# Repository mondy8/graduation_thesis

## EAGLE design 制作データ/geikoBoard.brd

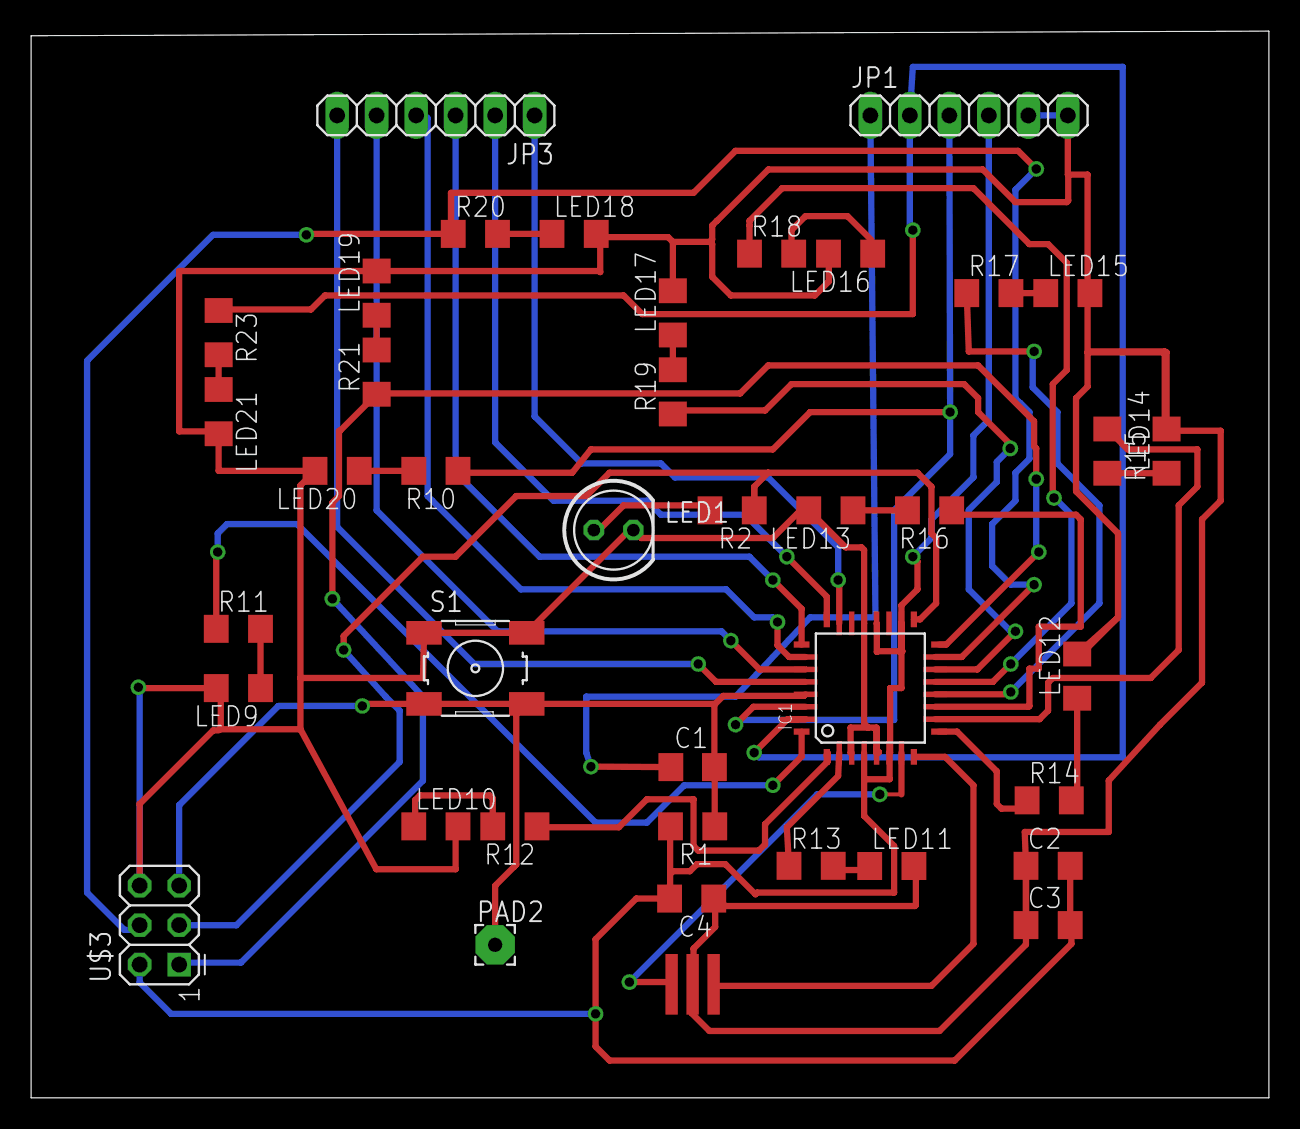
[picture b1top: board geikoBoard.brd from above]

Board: 2 copper layers, 79.6 x 68.6 mm, 40 parts (0 on the bottom side), 40 nets.

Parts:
C1: .1uf; C1206
C2: 1uf; 1206
C3: .1uf; 1206
C4: 10uf; 1206
IC1: ATMEGA48/88/168-AU; TQFP32-08
JP1, JP3: 1X06
LED1: LED5MM
LED9, LED10, LED11, LED12, LED13, LED14, LED15, LED16, LED17, LED18, LED19, LED20, LED21: 1206
PAD2: WIREPAD2,54/0,9; 2,54/0,9
R1: 10k; 1206
R2, R10, R11, R12, R13, R14, R15, R16, R17, R18, R19, R20, R21, R23: 499; 1206
S1: 6MM_SWITCH
U$2: RESONATOREFOB; EFOBM
U$3: AVRISP; 2X03

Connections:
DTR: C1.1, JP1.1
GND: C2.1, C3.1, C4.1, IC1.3, IC1.5, IC1.21, JP1.5, JP1.6, LED1.K, LED9.2, LED10.2, LED11.2, LED12.2, LED13.2, LED14.2, LED15.2, LED16.2, LED17.2, LED18.2, LED19.2, LED20.2, LED21.2, S1.1, S1.2, U$2.2, U$3.6
MISO: IC1.16, R21.1, U$3.1
MOSI: IC1.15, R20.1, U$3.4
unnamed: IC1.8, U$2.1
unnamed: IC1.12, R17.1
unnamed: IC1.23, JP3.1
unnamed: IC1.24, JP3.2
unnamed: IC1.25, JP3.3
unnamed: IC1.26, JP3.4
unnamed: IC1.27, JP3.5
unnamed: IC1.28, JP3.6
unnamed: IC1.7, U$2.3
unnamed: IC1.32, R11.1
unnamed: IC1.1, R12.1
unnamed: IC1.2, R13.1
unnamed: IC1.9, R14.1
unnamed: IC1.10, R15.1
unnamed: IC1.11, R16.1
unnamed: IC1.13, R18.1
unnamed: IC1.14, R19.1
unnamed: LED9.1, R11.2
unnamed: LED10.1, R12.2
unnamed: LED11.1, R13.2
unnamed: LED12.1, R14.2
unnamed: LED1.A, R2.2
unnamed: LED13.1, R16.2
unnamed: LED14.1, R15.2
unnamed: LED15.1, R17.2
unnamed: LED16.1, R18.2
unnamed: LED17.1, R19.2
unnamed: LED18.1, R20.2
unnamed: LED19.1, R21.2
unnamed: LED20.1, R10.2
unnamed: LED21.1, R23.2
RST: C1.2, IC1.29, PAD2.1, R1.1, S1.3, S1.4, U$3.5
RX: IC1.30, JP1.3, R10.1
SCK: IC1.17, R2.1, U$3.3
TX: IC1.31, JP1.2, R23.1
VCC: C2.2, C3.2, C4.2, IC1.4, IC1.6, IC1.18, IC1.20, JP1.4, R1.2, U$3.2

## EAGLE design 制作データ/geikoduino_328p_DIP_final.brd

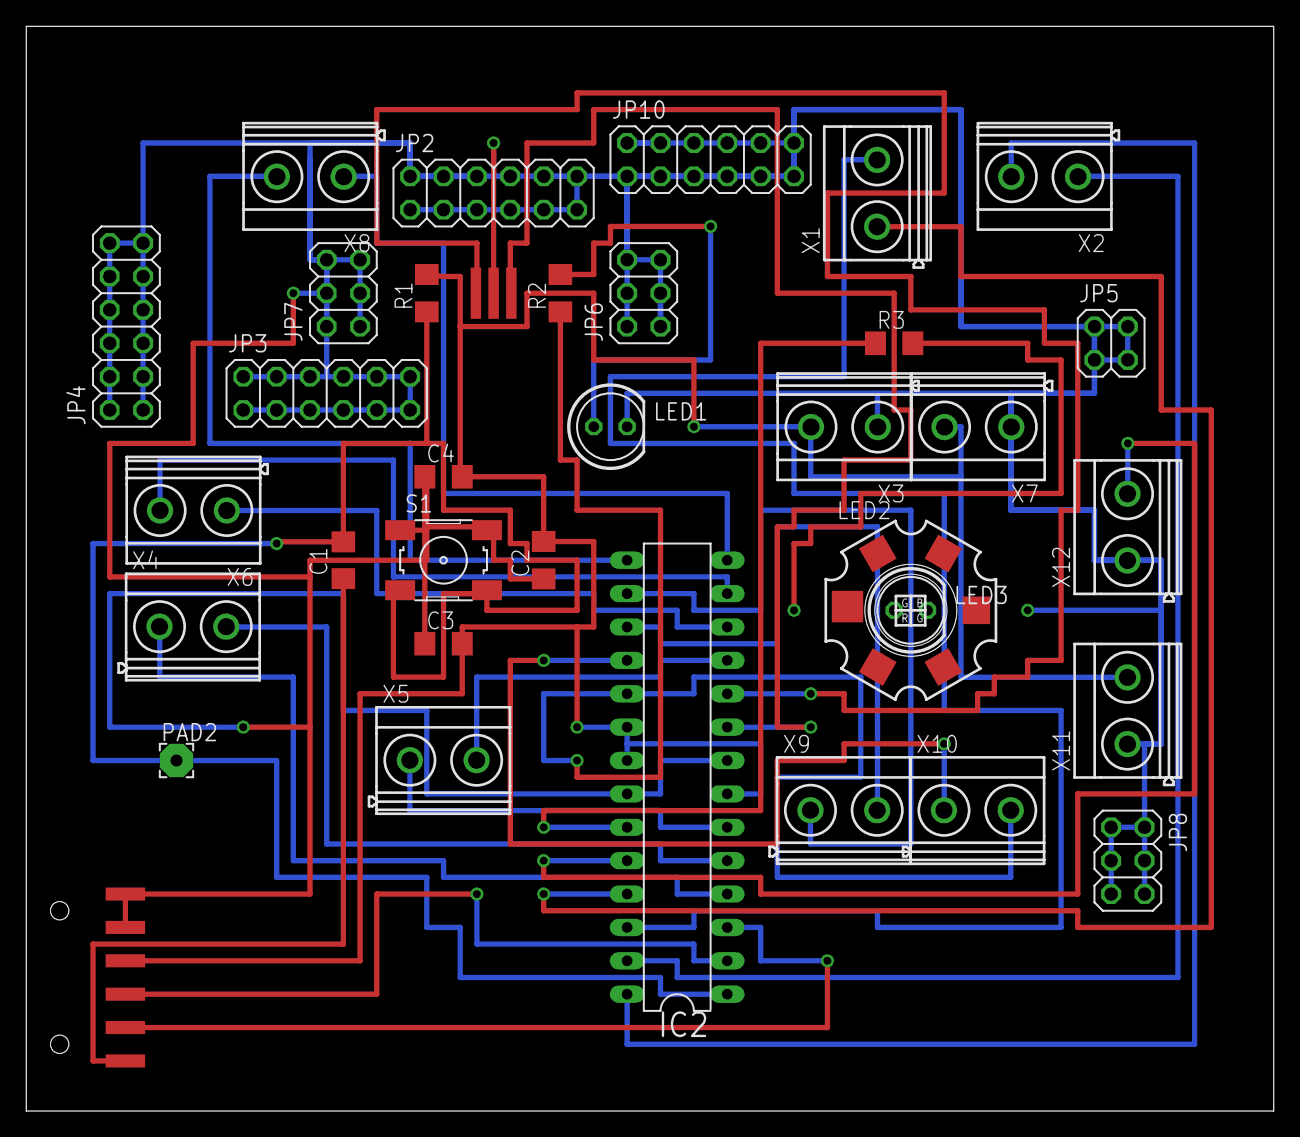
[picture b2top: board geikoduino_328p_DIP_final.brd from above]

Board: 2 copper layers, 94.9 x 82.5 mm, 35 parts (0 on the bottom side), 29 nets.

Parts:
C1: .1uf; C1206
C2: 1uf; 1206
C3: .1uf; 1206
C4: 10uf; 1206
IC2: ATMEGA328-20P; DIL28-3
JP1: 1X06-SMD
JP2, JP3, JP4, JP10: 2X06
JP5: 2X02
JP6, JP7, JP8: 2X03
LED1, LED3: LED5MM
LED2: ACULED-RGB
PAD2: WIREPAD2,54/0,9; 2,54/0,9
R1: 10k; 1206
R2: 499; 1206
R3: 7.14; 1206
S1: 6MM_SWITCH
U$2: RESONATOREFOB; EFOBM
X1, X2, X3, X4, X5, X6, X7, X8, X9, X10, X11, X12: MKDSN1,5/2-5,08

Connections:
DTR: C1.1, JP1.6
GND: C2.1, C3.1, C4.1, IC2.8, IC2.22, JP1.1, JP1.2, JP2.1, JP2.2, JP2.3, JP2.4, JP2.5, JP2.6, JP2.7, JP2.8, JP2.9, JP2.10, JP2.11, JP2.12, JP3.1, JP3.2, JP3.3, JP3.4, JP3.5, JP3.6, JP3.7, JP3.8, JP3.9, JP3.10, JP3.11, JP3.12, JP4.1, JP4.2, JP4.3, JP4.4, JP4.5, JP4.6, JP4.7, JP4.8, JP4.9, JP4.10, JP4.11, JP4.12, JP6.2, JP10.1, JP10.2, JP10.3, JP10.4, JP10.5, JP10.6, JP10.7, JP10.8, JP10.9, JP10.10, JP10.11, JP10.12, LED1.K, LED3.K, S1.1, S1.2, U$2.2, X3.1, X7.1, X11.1, X12.1
MISO: IC2.18, X10.1
MOSI: IC2.17, X9.2
unnamed: IC2.10, U$2.1
unnamed: IC2.14, X8.1
unnamed: IC2.23, R3.1
unnamed: IC2.24, X12.2
unnamed: IC2.25, X1.1
unnamed: IC2.26, X1.2
unnamed: IC2.27, X2.1
unnamed: IC2.28, X2.2
unnamed: IC2.9, U$2.3
unnamed: IC2.4, X4.1
unnamed: IC2.5, X4.2
unnamed: IC2.6, X5.1
unnamed: IC2.11, X5.2
unnamed: IC2.12, X6.1
unnamed: IC2.13, X6.2
unnamed: LED1.A, R2.2
unnamed: IC2.15, X8.2
unnamed: IC2.16, X9.1
unnamed: LED3.A, R3.2
unnamed: JP5.1, JP5.2, JP5.3, JP5.4, JP6.1, JP6.3, JP6.5, JP6.6, JP7.1, JP7.2, JP7.3, JP7.4, JP7.5, JP7.6, JP8.1, JP8.2, JP8.3, JP8.4, JP8.5, JP8.6
RST: C1.2, IC2.1, PAD2.1, R1.1, S1.3, S1.4
RX: IC2.2, JP1.4
SCK: IC2.19, R2.1, X10.2
TX: IC2.3, JP1.5
VCC: C2.2, C3.2, C4.2, IC2.7, IC2.20, IC2.21, JP1.3, R1.2, X3.2, X7.2, X11.2

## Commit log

2016-11-28 実例紹介追加
2016-12-01 背景課題など追加
2016-12-02 背景追加
2016-12-04 背景など追加
2016-12-06 ファイルのワード化 背景追加
2016-12-10 txtデータ削除、材料候補追加、背景を一部構成変更
2016-12-11 目次追加
2016-12-19 基板の歴史追加
2016-12-19 中間発表プレゼン追加
2016-12-28 制作したeagleデータ・画像の追加
2016-12-29 制作過程追加、geikoduino一つ目ミリング終える
2017-01-07 制作過程・基板作成の歴史追加
2017-01-08 １章書き始める
2017-01-09 １章、４章追加
2017-01-09 １章追加・４章を３章に変更
2017-01-10 アンケートを作成・１章と3章を追加
2017-01-15 研究の方向転換・GeikoBoard作成するも挫折
2017-01-17 挫折を乗り越える・概要を追加
2017-01-18 概要追加
2017-01-20 概要提出
2017-01-20 ファイルの整理、本文執筆開始
2017-01-20 本論文の型を作成
2017-01-23 本文執筆
2017-01-24 画像追加
2017-01-24 ユーザー評価を進める
2017-01-25 ユーザー評価更新
2017-01-25 いろいろ画像追加
2017-01-26 考察など追加
2017-01-26 最後らへん追加
2017-01-28 参考文献整理
2017-01-28 図の整理
2017-01-28 ところどころ追加
2017-01-28 第１版完成、か？
2017-01-30 結論の肉付け
2017-01-30 完成！！
2017-02-01 提出完了
2018-12-02 softrobot start
2018-12-17 ファイルの整理・稲研展の準備
2019-01-01 新年一発目 アンケート調査アンド枠組み整理
2019-01-02 シリコン生成方法記入
2019-01-06 3章 heart of mollusca 制作方法について詳細追加
2019-01-06 ４章少し追加
2019-01-08 アンケートを整理・グラフ化
2019-01-09 3・4・5章追加
2019-01-10 3・4章追加
2019-01-11 １・2章追加 google docsで作業開始
2019-01-16 ２章・５章・画像追加
2019-01-17 5章についてダメ出しをもらったので変更
2019-01-20 4・5・６章更新
2019-01-21 第１稿完成
2019-01-22 画像とか参照とか
2019-01-22 画像・参照文献追加終了
2019-01-23 目的と結論を調整
2019-01-24 おおづめ
2019-01-24 5章にまとめを加える
2019-01-24 とりあえず完成
2019-01-24 提出前夜
